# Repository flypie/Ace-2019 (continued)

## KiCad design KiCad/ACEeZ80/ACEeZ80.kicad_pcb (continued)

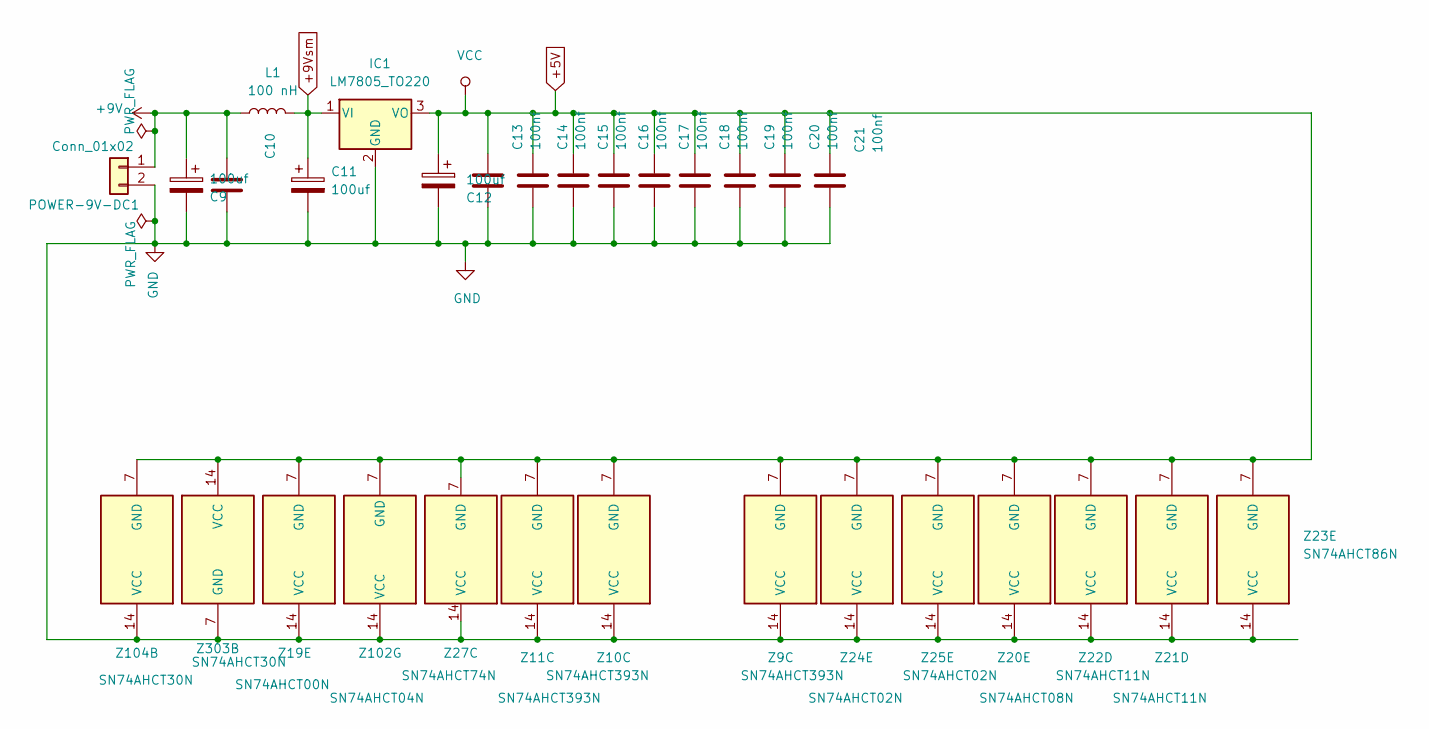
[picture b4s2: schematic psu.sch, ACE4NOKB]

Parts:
C9, C12: 100uf; CP_Radial_D5.0mm_P2.00mm
C10, C13, C14, C15, C16, C17, C18, C19, C20, C21: 100nf; C_Disc_D3.0mm_W1.6mm_P2.50mm; Manufacturer_Part_Number K104K10X7RF53H5
C11: 100uf; CP_Radial_D4.0mm_P1.50mm; Manufacturer_Part_Number K104K10X7RF53H5
IC1: LM7805_TO220; TO-220-3_Vertical
L1: 100 nH; KEMET_SBT_0260T
POWER-9V-DC1: Conn_01x02; CUI_PJ-036C
Z9, Z10, Z11: SN74AHCT393N; DIP-14_W7.62mm
Z19: SN74AHCT00N; DIP-14_W7.62mm
Z20: SN74AHCT08N; DIP-14_W7.62mm
Z21, Z22: SN74AHCT11N; DIP-14_W7.62mm
Z23: SN74AHCT86N; DIP-14_W7.62mm
Z24, Z25: SN74AHCT02N; DIP-14_W7.62mm
Z27: SN74AHCT74N; DIP-14_W7.62mm
Z102: SN74AHCT04N; DIP-14_W7.62mm
Z104: SN74AHCT30N; SOIC-14_3.9x8.7mm_P1.27mm; Manufacturer_Part_Number 74AHCT30D
Z303: SN74AHCT30N; SOIC-14_3.9x8.7mm_P1.27mm

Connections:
+9V: C9.1, C10.1, L1.1, POWER-9V-DC1.1
+9Vsm: C11.1, IC1.1 (VI), L1.2; also elsewhere on the board

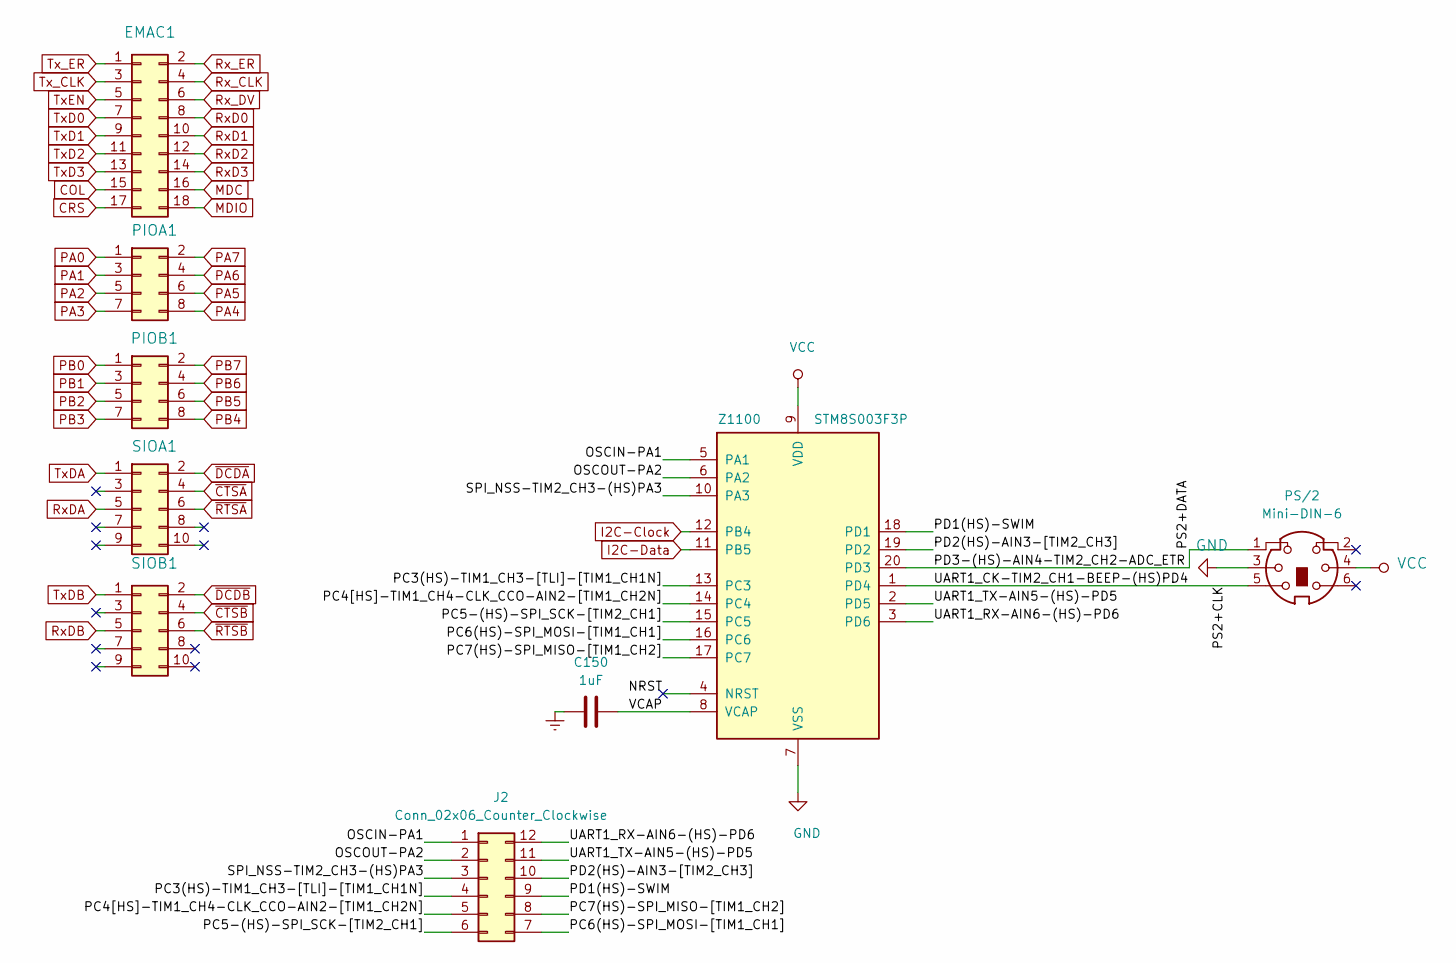
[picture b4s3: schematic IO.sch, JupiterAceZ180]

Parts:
C150: 1uF; C_Disc_D3.8mm_W2.6mm_P2.50mm
EMAC1: 2510-; PinHeader_2x09_P2.54mm_Vertical
J2: Conn_02x06_Counter_Clockwise; PinHeader_2x06_P2.54mm_Vertical
PIOA1: 2510-; PinHeader_2x04_P2.54mm_Vertical
PIOB1: 2510-; PinHeader_2x04_P2.54mm_Vertical
PS/2: Mini-DIN-6; 5749180-1
SIOA1: 2510-; PinHeader_2x05_P2.54mm_Vertical
SIOB1: 2510-; PinHeader_2x05_P2.54mm_Vertical
Z1100: STM8S003F3P; TSSOP-20_4.4x6.5mm_P0.65mm

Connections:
/IO/NRST: Z1100.4 (NRST)
/IO/OSCIN-PA1: J2.1, Z1100.5 (PA1)
/IO/OSCOUT-PA2: J2.2, Z1100.6 (PA2)
/IO/PC3(HS)-TIM1_CH3-[TLI]-[TIM1_CH1N]: J2.4, Z1100.13 (PC3)
/IO/PC4[HS]-TIM1_CH4-CLK_CCO-AIN2-[TIM1_CH2N]: J2.5, Z1100.14 (PC4)
/IO/PC5-(HS)-SPI_SCK-[TIM2_CH1]: J2.6, Z1100.15 (PC5)
/IO/PC6(HS)-SPI_MOSI-[TIM1_CH1]: J2.7, Z1100.16 (PC6)
/IO/PC7(HS)-SPI_MISO-[TIM1_CH2]: J2.8, Z1100.17 (PC7)
/IO/PD1(HS)-SWIM: J2.9, Z1100.18 (PD1)
/IO/PD2(HS)-AIN3-[TIM2_CH3]: J2.10, Z1100.19 (PD2)
/IO/PD3-(HS)-AIN4-TIM2_CH2-ADC_ETR: PS/2.1, Z1100.20 (PD3)
/IO/PS2+CLK: PS/2.5, Z1100.1 (PD4)
/IO/SPI_NSS-TIM2_CH3-(HS)PA3: J2.3, Z1100.10 (PA3)
/IO/UART1_RX-AIN6-(HS)-PD6: J2.12, Z1100.3 (PD6)
/IO/UART1_TX-AIN5-(HS)-PD5: J2.11, Z1100.2 (PD5)
/IO/VCAP: C150.1, Z1100.8 (VCAP)
COL: EMAC1.15; also elsewhere on the board
CRS: EMAC1.17; also elsewhere on the board
Earth: C150.2
I2C-Clock: Z1100.12 (PB4); also elsewhere on the board
I2C-Data: Z1100.11 (PB5); also elsewhere on the board
MDC: EMAC1.16; also elsewhere on the board
MDIO: EMAC1.18; also elsewhere on the board
PA0: PIOA1.1; also elsewhere on the board
PA1: PIOA1.3; also elsewhere on the board
PA2: PIOA1.5; also elsewhere on the board
PA3: PIOA1.7; also elsewhere on the board
PA4: PIOA1.8; also elsewhere on the board
PA5: PIOA1.6; also elsewhere on the board
PA6: PIOA1.4; also elsewhere on the board
PA7: PIOA1.2; also elsewhere on the board
PB0: PIOB1.1; also elsewhere on the board
PB1: PIOB1.3; also elsewhere on the board
PB2: PIOB1.5; also elsewhere on the board
PB3: PIOB1.7; also elsewhere on the board
PB4: PIOB1.8; also elsewhere on the board
PB5: PIOB1.6; also elsewhere on the board
PB6: PIOB1.4; also elsewhere on the board
PB7: PIOB1.2; also elsewhere on the board
RxD0: EMAC1.8; also elsewhere on the board
RxD1: EMAC1.10; also elsewhere on the board
RxD2: EMAC1.12; also elsewhere on the board
RxD3: EMAC1.14; also elsewhere on the board
RxDA: SIOA1.5; also elsewhere on the board
RxDB: SIOB1.5; also elsewhere on the board
Rx_CLK: EMAC1.4; also elsewhere on the board
Rx_DV: EMAC1.6; also elsewhere on the board
Rx_ER: EMAC1.2; also elsewhere on the board
TxD0: EMAC1.7; also elsewhere on the board
TxD1: EMAC1.9; also elsewhere on the board
TxD2: EMAC1.11; also elsewhere on the board
TxD3: EMAC1.13; also elsewhere on the board
TxDA: SIOA1.1; also elsewhere on the board
TxDB: SIOB1.1; also elsewhere on the board
TxEN: EMAC1.5; also elsewhere on the board
Tx_CLK: EMAC1.3; also elsewhere on the board
Tx_ER: EMAC1.1; also elsewhere on the board
~CTSA: SIOA1.4; also elsewhere on the board
~CTSB: SIOB1.4; also elsewhere on the board
~DCDA: SIOA1.2; also elsewhere on the board
~DCDB: SIOB1.2; also elsewhere on the board
~RTSA: SIOA1.6; also elsewhere on the board
~RTSB: SIOB1.6; also elsewhere on the board

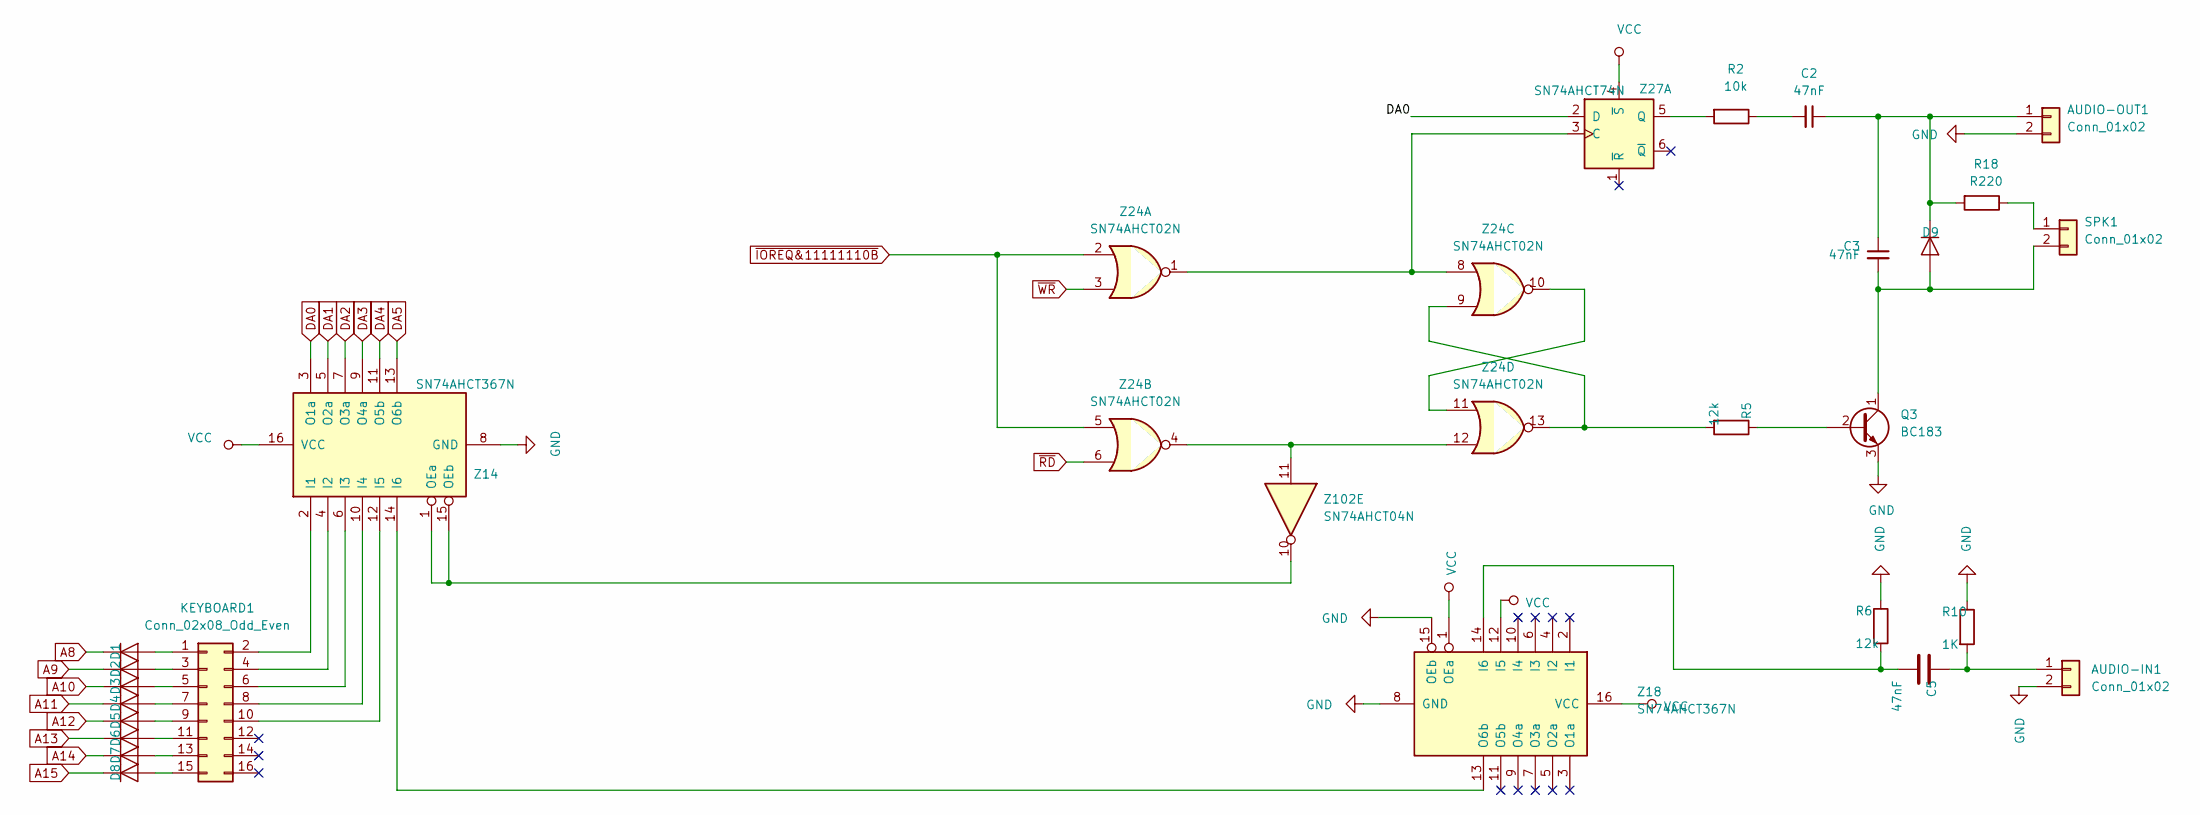
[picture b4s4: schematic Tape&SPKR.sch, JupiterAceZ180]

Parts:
AUDIO-IN1: Conn_01x02; PinHeader_1x02_P2.54mm_Vertical
AUDIO-OUT1: Conn_01x02; PinHeader_1x02_P2.54mm_Vertical
C2, C3, C5: 47nF; C_Disc_D5.0mm_W2.5mm_P5.00mm
D1, D2, D3, D4, D5, D6, D7, D8, D9: 1N4148; D_DO-35_SOD27_P2.54mm_Vertical_AnodeUp
KEYBOARD1: Conn_02x08_Odd_Even; PinHeader_2x08_P2.54mm_Vertical
Q3: BC183; TO-92_Inline
R2: 10k; R_Axial_DIN0204_L3.6mm_D1.6mm_P2.54mm_Vertical
R5, R6: 12k; R_Axial_DIN0204_L3.6mm_D1.6mm_P2.54mm_Vertical
R10: 1K; R_Axial_DIN0204_L3.6mm_D1.6mm_P2.54mm_Vertical
R18: R220; R_Axial_DIN0204_L3.6mm_D1.6mm_P1.90mm_Vertical
SPK1: Conn_01x02; PinHeader_1x02_P2.54mm_Vertical
Z14, Z18: SN74AHCT367N; DIP-16_W7.62mm
Z24: SN74AHCT02N; DIP-14_W7.62mm
Z27: SN74AHCT74N; DIP-14_W7.62mm
Z102: SN74AHCT04N; DIP-14_W7.62mm

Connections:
A8: D1.1 (K); also elsewhere on the board
A9: D2.1 (K); also elsewhere on the board
A10: D3.1 (K); also elsewhere on the board
A11: D4.1 (K); also elsewhere on the board
A12: D5.1 (K); also elsewhere on the board
A13: D6.1 (K); also elsewhere on the board
A14: D7.1 (K); also elsewhere on the board
A15: D8.1 (K); also elsewhere on the board
DA0: Z14.3 (O1a), Z27.2 (D); also elsewhere on the board
DA1: Z14.5 (O2a); also elsewhere on the board
DA2: Z14.7 (O3a); also elsewhere on the board
DA3: Z14.9 (O4a); also elsewhere on the board
DA4: Z14.11 (O5b); also elsewhere on the board
DA5: Z14.13 (O6b); also elsewhere on the board
unnamed: AUDIO-IN1.1, C5.1, R10.2
unnamed: AUDIO-OUT1.1, C2.1, C3.1, D9.1 (K), R18.2
unnamed: C2.2, R2.1
unnamed: C3.2, D9.2 (A), Q3.1 (C), SPK1.2
unnamed: C5.2, R6.2, Z18.14 (I6)
unnamed: D1.2 (A), KEYBOARD1.1
unnamed: D2.2 (A), KEYBOARD1.3
unnamed: D3.2 (A), KEYBOARD1.5
unnamed: D4.2 (A), KEYBOARD1.7
unnamed: D5.2 (A), KEYBOARD1.9
unnamed: D6.2 (A), KEYBOARD1.11
unnamed: D7.2 (A), KEYBOARD1.13
unnamed: D8.2 (A), KEYBOARD1.15
unnamed: KEYBOARD1.2, Z14.2 (I1)
unnamed: KEYBOARD1.4, Z14.4 (I2)
unnamed: KEYBOARD1.6, Z14.6 (I3)
unnamed: KEYBOARD1.8, Z14.10 (I4)
unnamed: KEYBOARD1.10, Z14.12 (I5)
unnamed: Q3.2 (B), R5.1
unnamed: R2.2, Z27.5 (Q)
unnamed: R5.2, Z24.9, Z24.13
unnamed: R18.1, SPK1.1
unnamed: Z14.14 (I6), Z18.13 (O6b)
unnamed: Z24.1, Z24.8, Z27.3 (C)
unnamed: Z24.10, Z24.11
unnamed: Z14.1 (OEa), Z14.15 (OEb), Z102.10
unnamed: Z24.4, Z24.12, Z102.11
~IOREQ&11111110B: Z24.2, Z24.5; also elsewhere on the board
~RD: Z24.6; also elsewhere on the board
~WR: Z24.3; also elsewhere on the board

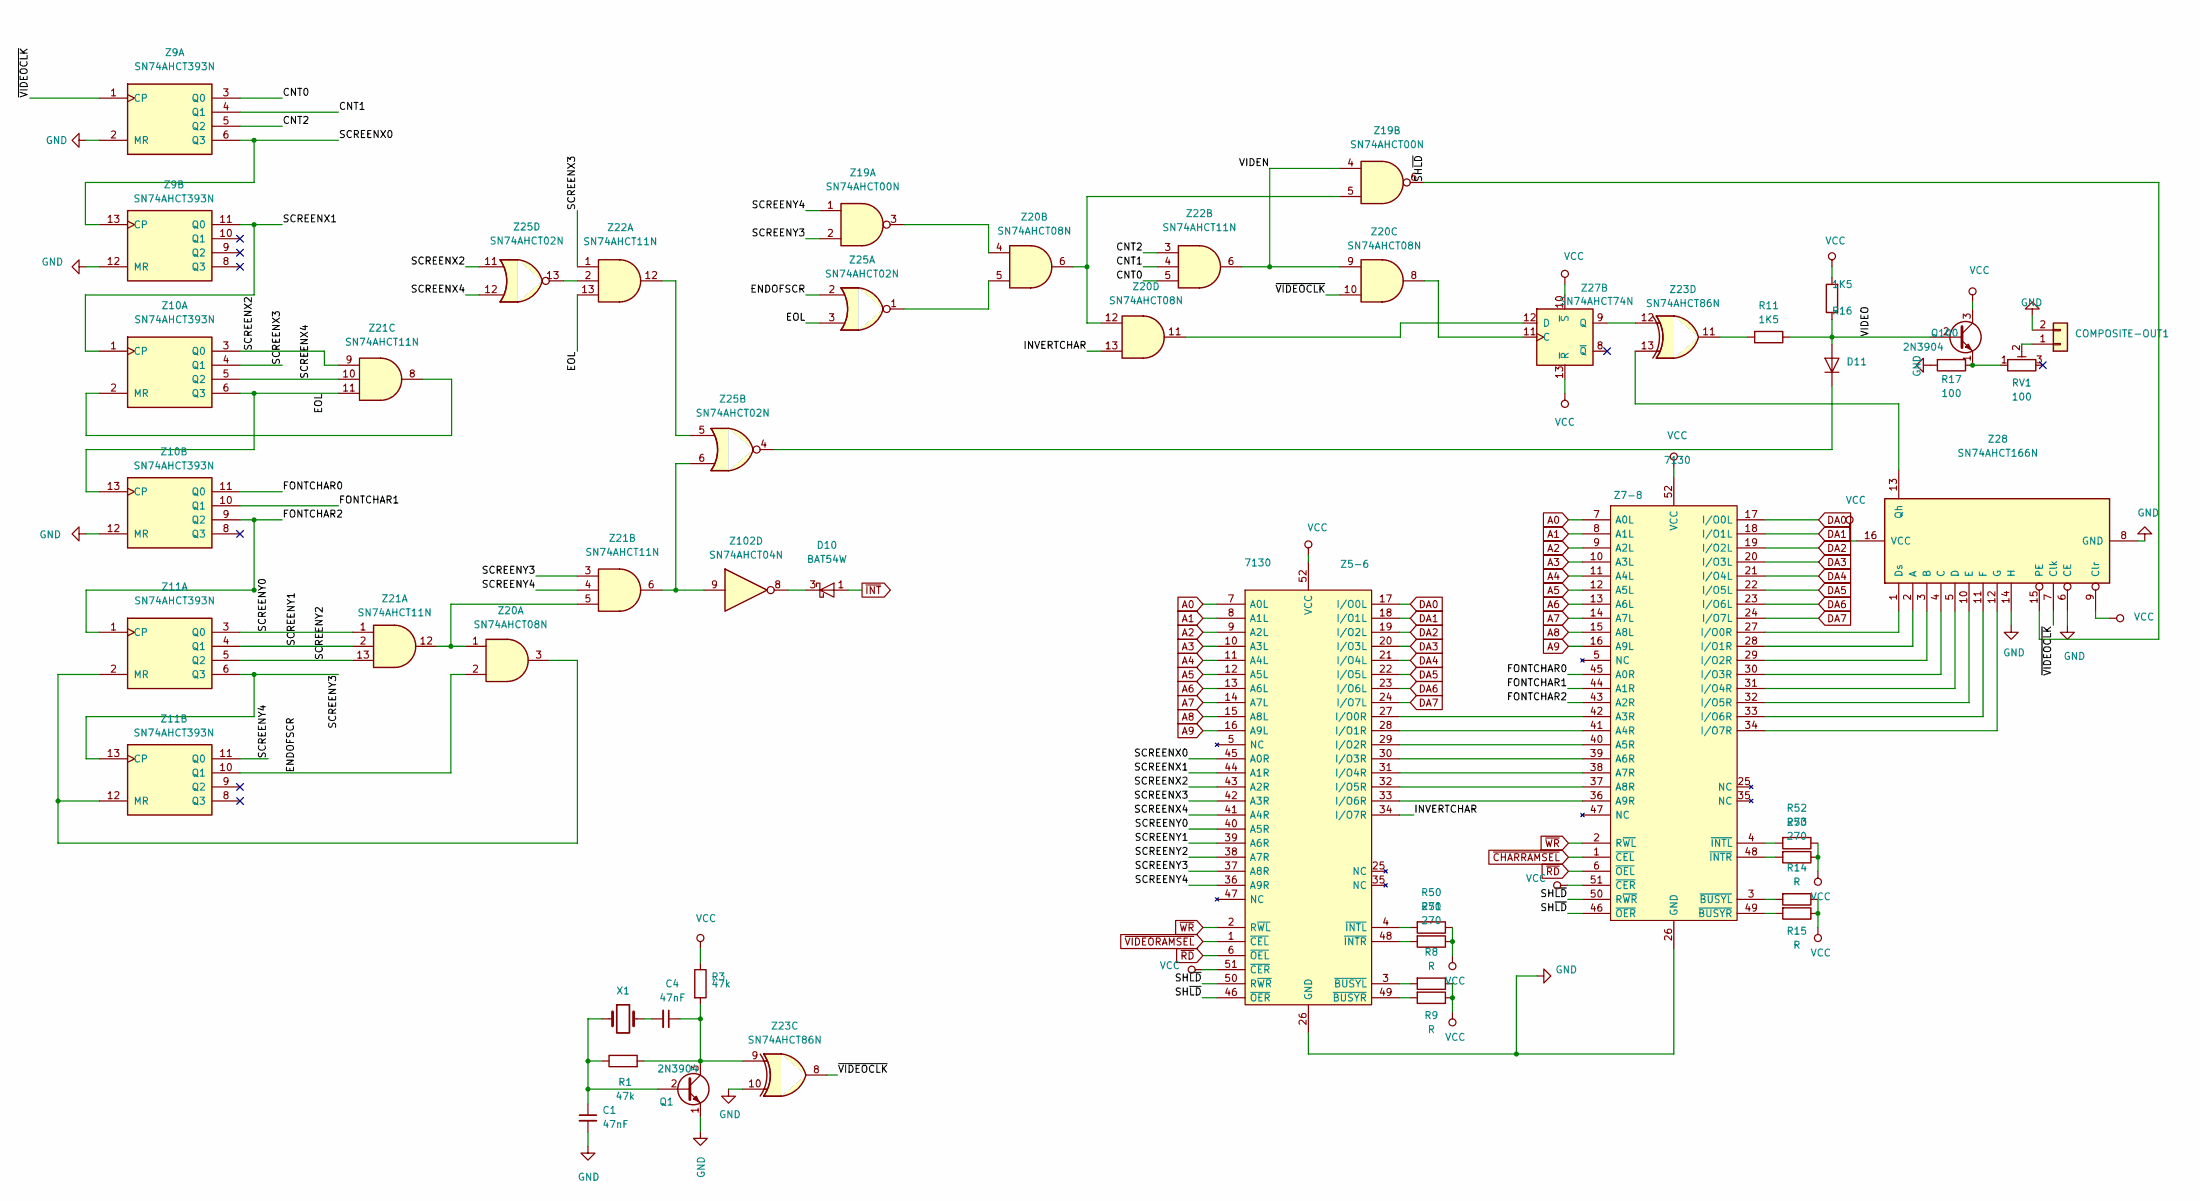
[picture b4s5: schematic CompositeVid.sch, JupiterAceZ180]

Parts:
C1, C4: 47nF; C_Disc_D5.0mm_W2.5mm_P5.00mm
COMPOSITE-OUT1: COMPOSITE-OUT1; PinHeader_1x02_P2.54mm_Vertical
D10: BAT54W; SOT-323_SC-70
D11: 1N4148; D_DO-35_SOD27_P2.54mm_Vertical_AnodeUp
Q1, Q100: 2N3904; TO-92_Inline
R1, R3: 47k; R_Axial_DIN0204_L3.6mm_D1.6mm_P1.90mm_Vertical
R8, R9, R14, R15: R; R_Axial_DIN0204_L3.6mm_D1.6mm_P2.54mm_Vertical
R11, R16: 1K5; R_Axial_DIN0204_L3.6mm_D1.6mm_P2.54mm_Vertical
R17: 100; R_Axial_DIN0204_L3.6mm_D1.6mm_P1.90mm_Vertical
R50, R51, R52, R53: 270; R_Axial_DIN0204_L3.6mm_D1.6mm_P2.54mm_Vertical
RV1: 100; 3362H1103LF
X1: CRYSTALHC49U-V 6.556MHz; Crystal_HC49-U_Vertical
Z5-6, Z7-8: 7130; PLCC-52_THT-Socket; Manufacturer_Part_Number 7132LA100PDG
Z9, Z10, Z11: SN74AHCT393N; DIP-14_W7.62mm
Z19: SN74AHCT00N; DIP-14_W7.62mm
Z20: SN74AHCT08N; DIP-14_W7.62mm
Z21, Z22: SN74AHCT11N; DIP-14_W7.62mm
Z23: SN74AHCT86N; DIP-14_W7.62mm
Z25: SN74AHCT02N; DIP-14_W7.62mm
Z27: SN74AHCT74N; DIP-14_W7.62mm
Z28: SN74AHCT166N; DIP-16_W7.62mm
Z102: SN74AHCT04N; DIP-14_W7.62mm

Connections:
/CompositeVid/CNT0: Z9.3 (Q0), Z22.5
/CompositeVid/CNT1: Z9.4 (Q1), Z22.4
/CompositeVid/CNT2: Z9.5 (Q2), Z22.3
/CompositeVid/ENDOFSCR: Z11.10 (Q1), Z20.2, Z25.2
/CompositeVid/EOL: Z10.6 (Q3), Z10.13 (CP), Z21.11, Z22.13, Z25.3
/CompositeVid/FONTCHAR0: Z7-8.45 (A0R), Z10.11 (Q0)
/CompositeVid/FONTCHAR1: Z7-8.44 (A1R), Z10.10 (Q1)
/CompositeVid/FONTCHAR2: Z7-8.43 (A2R), Z10.9 (Q2), Z11.1 (CP)
/CompositeVid/INVERTCHAR: Z5-6.34 (I/O7R), Z20.13
/CompositeVid/SCREENX0: Z5-6.45 (A0R), Z9.6 (Q3), Z9.13 (CP)
/CompositeVid/SCREENX1: Z5-6.44 (A1R), Z9.11 (Q0), Z10.1 (CP)
/CompositeVid/SCREENX2: Z5-6.43 (A2R), Z10.3 (Q0), Z21.9, Z25.11
/CompositeVid/SCREENX3: Z5-6.42 (A3R), Z10.4 (Q1), Z22.1
/CompositeVid/SCREENX4: Z5-6.41 (A4R), Z10.5 (Q2), Z21.10, Z25.12
/CompositeVid/SCREENY0: Z5-6.40 (A5R), Z11.3 (Q0), Z21.1
/CompositeVid/SCREENY1: Z5-6.39 (A6R), Z11.4 (Q1), Z21.2
/CompositeVid/SCREENY2: Z5-6.38 (A7R), Z11.5 (Q2), Z21.13
/CompositeVid/SCREENY3: Z5-6.37 (A8R), Z11.6 (Q3), Z11.13 (CP), Z19.2, Z21.3
/CompositeVid/SCREENY4: Z5-6.36 (A9R), Z11.11 (Q0), Z19.1, Z21.4
/CompositeVid/SH~LD: Z5-6.46 (~OER), Z5-6.50 (R~WR), Z7-8.46 (~OER), Z7-8.50 (R~WR), Z19.6, Z28.15 (PE)
/CompositeVid/VIDEN: Z19.4, Z20.9, Z22.6
/CompositeVid/VIDEO: D11.2 (A), Q100.2 (B), R11.1, R16.1
/CompositeVid/~VIDEOCLK: Z9.1 (CP), Z20.10, Z23.8, Z28.7 (Clk)
A0: Z5-6.7 (A0L), Z7-8.7 (A0L); also elsewhere on the board
A1: Z5-6.8 (A1L), Z7-8.8 (A1L); also elsewhere on the board
A2: Z5-6.9 (A2L), Z7-8.9 (A2L); also elsewhere on the board
A3: Z5-6.10 (A3L), Z7-8.10 (A3L); also elsewhere on the board
A4: Z5-6.11 (A4L), Z7-8.11 (A4L); also elsewhere on the board
A5: Z5-6.12 (A5L), Z7-8.12 (A5L); also elsewhere on the board
A6: Z5-6.13 (A6L), Z7-8.13 (A6L); also elsewhere on the board
A7: Z5-6.14 (A7L), Z7-8.14 (A7L); also elsewhere on the board
A8: Z5-6.15 (A8L), Z7-8.15 (A8L); also elsewhere on the board
A9: Z5-6.16 (A9L), Z7-8.16 (A9L); also elsewhere on the board
DA0: Z5-6.17 (I/O0L), Z7-8.17 (I/O0L); also elsewhere on the board
DA1: Z5-6.18 (I/O1L), Z7-8.18 (I/O1L); also elsewhere on the board
DA2: Z5-6.19 (I/O2L), Z7-8.19 (I/O2L); also elsewhere on the board
DA3: Z5-6.20 (I/O3L), Z7-8.20 (I/O3L); also elsewhere on the board
DA4: Z5-6.21 (I/O4L), Z7-8.21 (I/O4L); also elsewhere on the board
DA5: Z5-6.22 (I/O5L), Z7-8.22 (I/O5L); also elsewhere on the board
DA6: Z5-6.23 (I/O6L), Z7-8.23 (I/O6L); also elsewhere on the board
DA7: Z5-6.24 (I/O7L), Z7-8.24 (I/O7L); also elsewhere on the board
unnamed: C1.1, Q1.2 (B), R1.1, X1.1
unnamed: C4.1, Q1.3 (C), R1.2, R3.2, Z23.9
unnamed: C4.2, X1.2
unnamed: COMPOSITE-OUT1.1, RV1.2
unnamed: D10.3 (K), Z102.8
unnamed: D11.1 (K), Z25.4
unnamed: Q100.1 (E), R17.1, RV1.1
unnamed: R8.2, Z5-6.3 (~BUSYL)
unnamed: R9.2, Z5-6.49 (~BUSYR)
unnamed: R11.2, Z23.11
unnamed: R14.2, Z7-8.3 (~BUSYL)
unnamed: R15.2, Z7-8.49 (~BUSYR)
unnamed: R50.2, Z5-6.4 (~INTL)
unnamed: R51.2, Z5-6.48 (~INTR)
unnamed: R52.2, Z7-8.4 (~INTL)
unnamed: R53.2, Z7-8.48 (~INTR)
unnamed: Z5-6.27 (I/O0R), Z7-8.42 (A3R)
unnamed: Z5-6.28 (I/O1R), Z7-8.41 (A4R)
unnamed: Z5-6.29 (I/O2R), Z7-8.40 (A5R)
unnamed: Z5-6.30 (I/O3R), Z7-8.39 (A6R)
unnamed: Z5-6.31 (I/O4R), Z7-8.38 (A7R)
unnamed: Z5-6.32 (I/O5R), Z7-8.37 (A8R)
unnamed: Z5-6.33 (I/O6R), Z7-8.36 (A9R)
unnamed: Z10.2 (MR), Z21.8
unnamed: Z11.2 (MR), Z11.12 (MR), Z20.3
unnamed: Z19.3, Z20.4
unnamed: Z19.5, Z20.6, Z20.12
unnamed: Z20.1, Z21.5, Z21.12
unnamed: Z20.5, Z25.1
unnamed: Z20.8, Z27.11 (C)
unnamed: Z20.11, Z27.12 (D)
unnamed: Z22.2, Z25.13
unnamed: Z22.12, Z25.5
unnamed: Z23.12, Z27.9 (Q)
unnamed: Z23.13, Z28.13 (Qh)
unnamed: Z7-8.27 (I/O0R), Z28.1 (Ds)
unnamed: Z7-8.28 (I/O1R), Z28.2 (A)
unnamed: Z7-8.29 (I/O2R), Z28.3 (B)
unnamed: Z7-8.30 (I/O3R), Z28.4 (C)
unnamed: Z7-8.31 (I/O4R), Z28.5 (D)
unnamed: Z7-8.32 (I/O5R), Z28.10 (E)
unnamed: Z7-8.33 (I/O6R), Z28.11 (F)
unnamed: Z7-8.34 (I/O7R), Z28.12 (G)
unnamed: Z21.6, Z25.6, Z102.9
~CHARRAMSEL: Z7-8.1 (~CEL); also elsewhere on the board
~INT: D10.1 (A); also elsewhere on the board
~RD: Z5-6.6 (~OEL), Z7-8.6 (~OEL); also elsewhere on the board
~VIDEORAMSEL: Z5-6.1 (~CEL); also elsewhere on the board
~WR: Z5-6.2 (R~WL), Z7-8.2 (R~WL); also elsewhere on the board

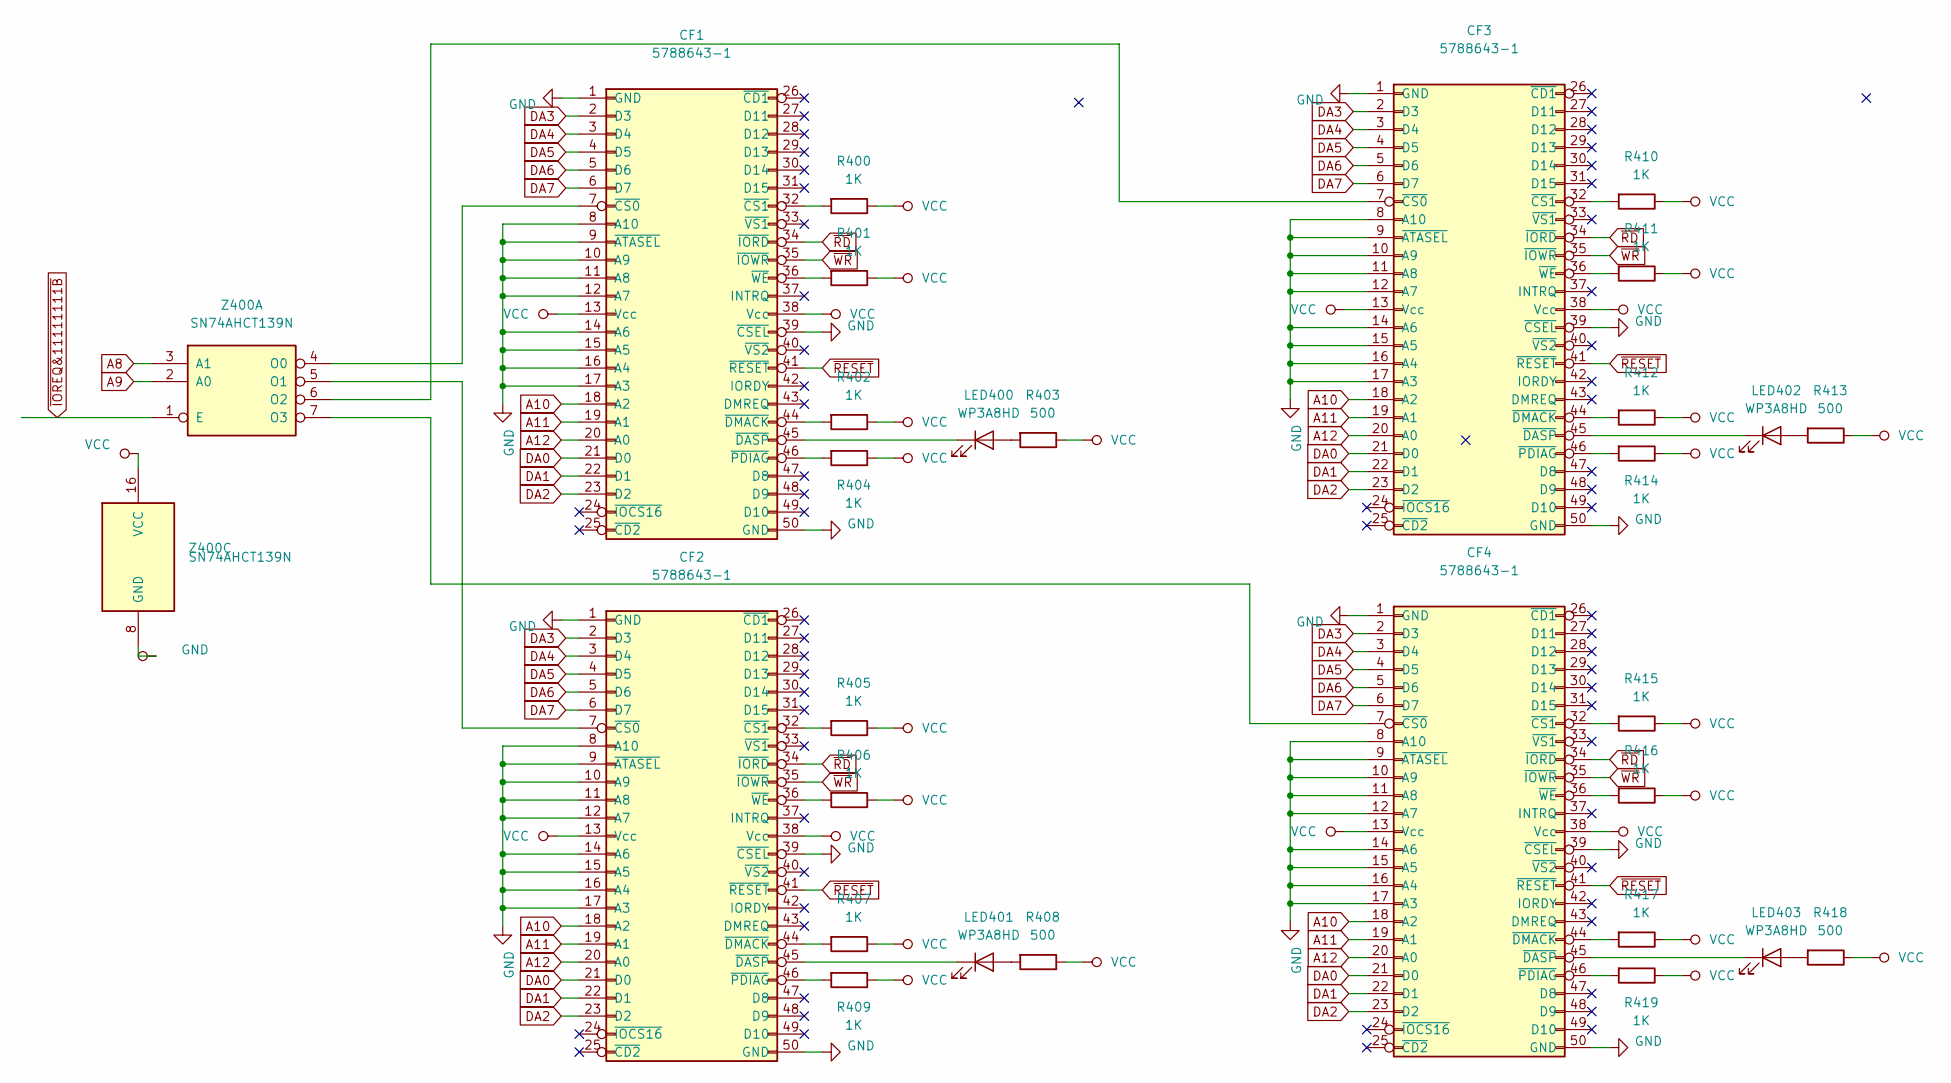
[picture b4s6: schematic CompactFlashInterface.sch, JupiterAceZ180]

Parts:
CF1, CF2, CF3, CF4: 5788643-1; 57886431; Manufacturer_Part_Number 5788643-1; Mouser Part Number 571-5788643-1
LED400, LED401, LED402, LED403: WP3A8HD; LED_D3.0mm
R400, R401, R402, R404, R405, R406, R407, R409, R410, R411, R412, R414, R415, R416, R417, R419: 1K; R_Axial_DIN0204_L3.6mm_D1.6mm_P1.90mm_Vertical
R403, R408, R413, R418: 500; R_Axial_DIN0204_L3.6mm_D1.6mm_P1.90mm_Vertical
Z400: SN74AHCT139N; DIP-16_W7.62mm

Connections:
A8: Z400.3 (A1); also elsewhere on the board
A9: Z400.2 (A0); also elsewhere on the board
A10: CF1.18 (A2), CF2.18 (A2), CF3.18 (A2), CF4.18 (A2); also elsewhere on the board
A11: CF1.19 (A1), CF2.19 (A1), CF3.19 (A1), CF4.19 (A1); also elsewhere on the board
A12: CF1.20 (A0), CF2.20 (A0), CF3.20 (A0), CF4.20 (A0); also elsewhere on the board
DA0: CF1.21 (D0), CF2.21 (D0), CF3.21 (D0), CF4.21 (D0); also elsewhere on the board
DA1: CF1.22 (D1), CF2.22 (D1), CF3.22 (D1), CF4.22 (D1); also elsewhere on the board
DA2: CF1.23 (D2), CF2.23 (D2), CF3.23 (D2), CF4.23 (D2); also elsewhere on the board
DA3: CF1.2 (D3), CF2.2 (D3), CF3.2 (D3), CF4.2 (D3); also elsewhere on the board
DA4: CF1.3 (D4), CF2.3 (D4), CF3.3 (D4), CF4.3 (D4); also elsewhere on the board
DA5: CF1.4 (D5), CF2.4 (D5), CF3.4 (D5), CF4.4 (D5); also elsewhere on the board
DA6: CF1.5 (D6), CF2.5 (D6), CF3.5 (D6), CF4.5 (D6); also elsewhere on the board
DA7: CF1.6 (D7), CF2.6 (D7), CF3.6 (D7), CF4.6 (D7); also elsewhere on the board
unnamed: CF1.7 (~CS0), Z400.4 (O0)
unnamed: CF1.32 (~CS1), R400.2
unnamed: CF1.36 (~WE), R401.2
unnamed: CF1.44 (~DMACK), R402.2
unnamed: CF1.45 (~DASP), LED400.1 (K)
unnamed: CF1.46 (~PDIAG), R404.2
unnamed: CF2.7 (~CS0), Z400.5 (O1)
unnamed: CF2.32 (~CS1), R405.2
unnamed: CF2.36 (~WE), R406.2
unnamed: CF2.44 (~DMACK), R407.2
unnamed: CF2.45 (~DASP), LED401.1 (K)
unnamed: CF2.46 (~PDIAG), R409.2
unnamed: CF3.7 (~CS0), Z400.6 (O2)
unnamed: CF3.32 (~CS1), R410.2
unnamed: CF3.36 (~WE), R411.2
unnamed: CF3.44 (~DMACK), R412.2
unnamed: CF3.45 (~DASP), LED402.1 (K)
unnamed: CF3.46 (~PDIAG), R414.2
unnamed: CF4.7 (~CS0), Z400.7 (O3)
unnamed: CF4.32 (~CS1), R415.2
unnamed: CF4.36 (~WE), R416.2
unnamed: CF4.44 (~DMACK), R417.2
unnamed: CF4.45 (~DASP), LED403.1 (K)
unnamed: CF4.46 (~PDIAG), R419.2
unnamed: LED400.2 (A), R403.2
unnamed: LED401.2 (A), R408.2
unnamed: LED402.2 (A), R413.2
unnamed: LED403.2 (A), R418.2
~IOREQ&11111111B: Z400.1 (E); also elsewhere on the board
~RD: CF1.34 (~IORD), CF2.34 (~IORD), CF3.34 (~IORD), CF4.34 (~IORD); also elsewhere on the board
~RESET: CF1.41 (~RESET), CF2.41 (~RESET), CF3.41 (~RESET), CF4.41 (~RESET); also elsewhere on the board
~WR: CF1.35 (~IOWR), CF2.35 (~IOWR), CF3.35 (~IOWR), CF4.35 (~IOWR); also elsewhere on the board

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
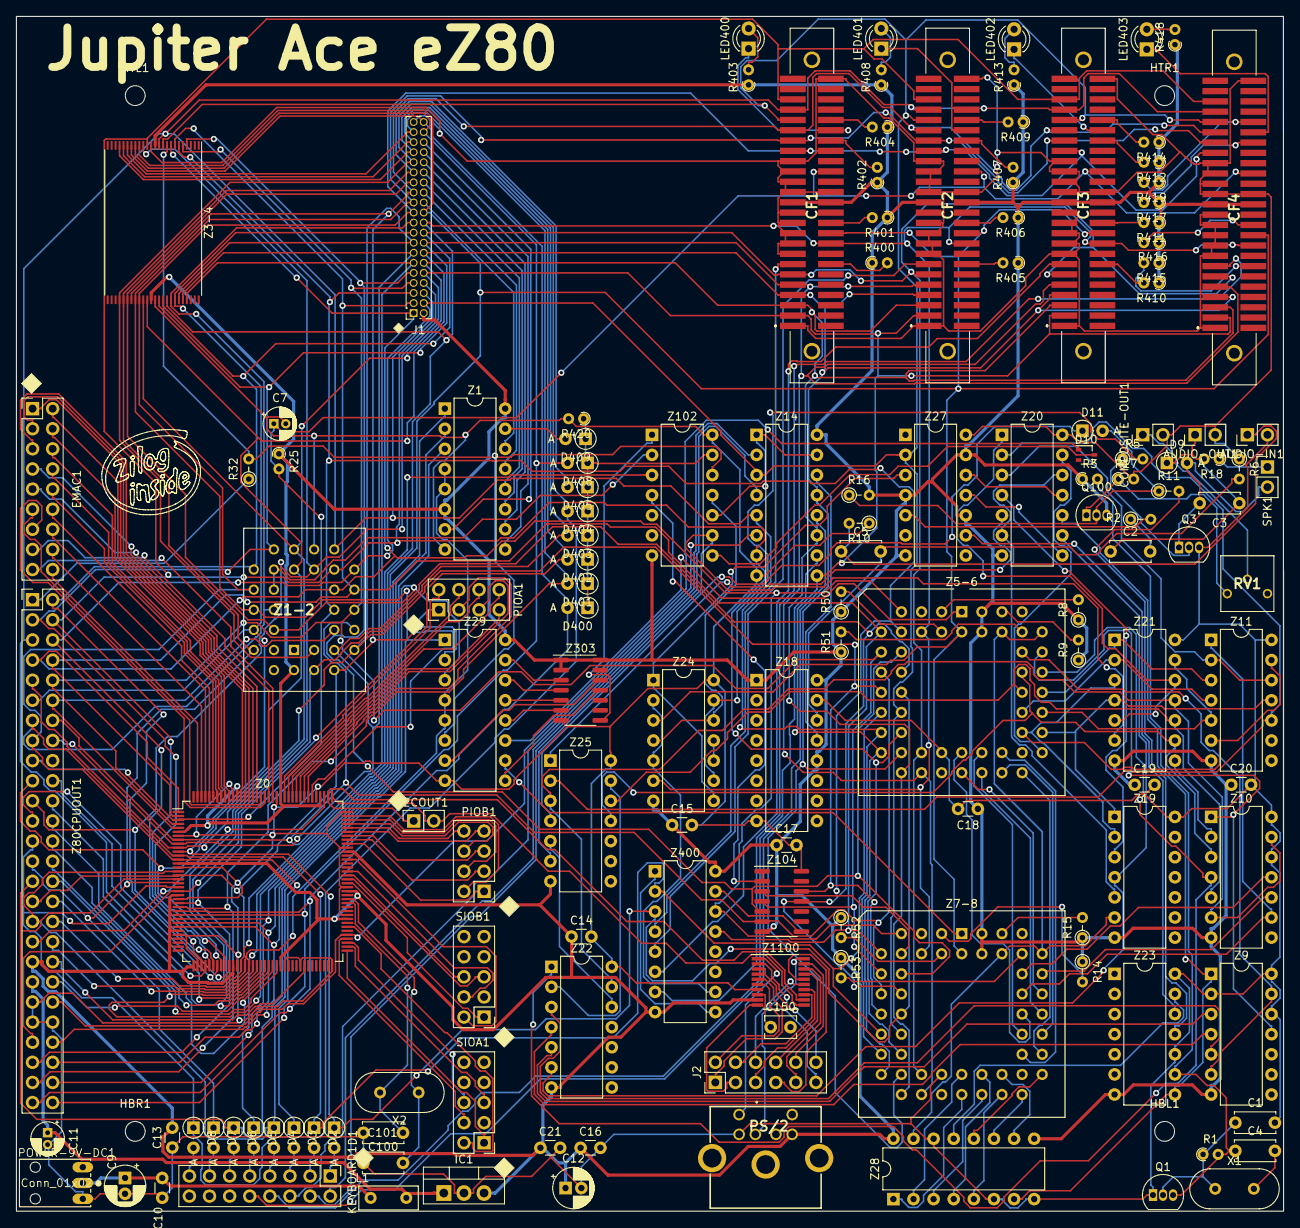
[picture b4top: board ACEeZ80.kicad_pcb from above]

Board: 2 copper layers, 160.0 x 150.9 mm, 146 parts (0 on the bottom side), 259 nets.

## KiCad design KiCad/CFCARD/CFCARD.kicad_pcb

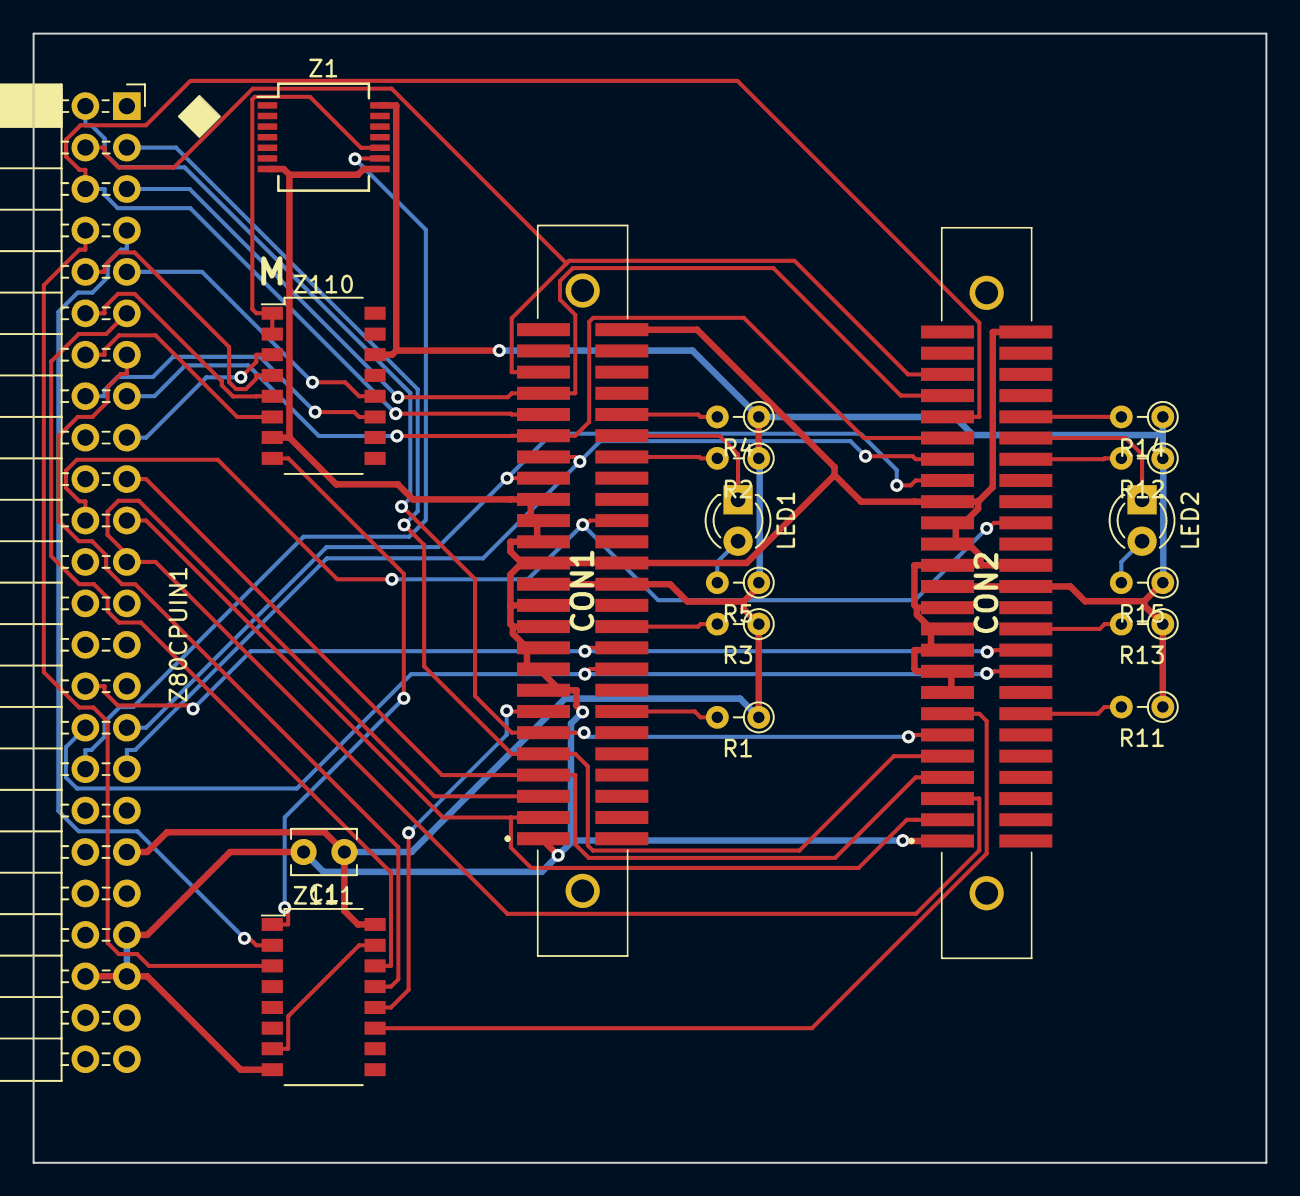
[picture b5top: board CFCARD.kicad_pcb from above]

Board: 2 copper layers, 75.6 x 69.2 mm, 19 parts (0 on the bottom side), 44 nets.

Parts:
C1: 0.1 uF; C_Disc_D3.8mm_W2.6mm_P2.50mm
CON1, CON2: 5788643-1; 57886431
LED1, LED2: LED; LED_D3.0mm
R1, R2, R3, R4, R11, R12, R13, R14: 1K; R_Axial_DIN0204_L3.6mm_D1.6mm_P2.54mm_Vertical
R5, R15: 560; R_Axial_DIN0204_L3.6mm_D1.6mm_P2.54mm_Vertical
Z1: SN74AHCT02PWR; SSOP-14_5.3x6.2mm_P0.65mm
Z80CPUIN1: Conn_02x24_Odd_Even; PinSocket_2x24_P2.54mm_Horizontal
Z110: 74AHCT30PW,118; SOP-16_4.4x10.4mm_P1.27mm
Z111: SN74AHCT139D; SOP-16_4.4x10.4mm_P1.27mm

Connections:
/A0: Z80CPUIN1.7, Z111.2 (A0)
/A1: Z80CPUIN1.8, Z111.3 (A1)
/A2: Z80CPUIN1.17, Z110.3
/A3: Z80CPUIN1.10, Z110.4
/A4: Z80CPUIN1.12, Z110.5
/A5: Z80CPUIN1.14, Z110.6
/A6: Z80CPUIN1.16, Z110.11
/A7: Z80CPUIN1.9, Z110.12
/A8: Z80CPUIN1.11, Z111.14 (A0)
/A9: Z80CPUIN1.13, Z111.13 (A1)
/A10: CON1.20 (A0), CON2.20 (A0), Z80CPUIN1.15
/A11: CON1.19 (A1), CON2.19 (A1), Z80CPUIN1.33
/A12: CON1.18 (A2), CON2.18 (A2), Z80CPUIN1.31
/DA0: CON1.21 (D0), CON2.21 (D0), Z80CPUIN1.6
/DA1: CON1.22 (D1), CON2.22 (D1), Z80CPUIN1.5
/DA2: CON1.23 (D2), CON2.23 (D2), Z80CPUIN1.4
/DA3: CON1.2 (D3), CON2.2 (D3), Z80CPUIN1.21
/DA4: CON1.3 (D4), CON2.3 (D4), Z80CPUIN1.23
/DA5: CON1.4 (D5), CON2.4 (D5), Z80CPUIN1.19
/DA6: CON1.5 (D6), CON2.5 (D6), Z80CPUIN1.3
/DA7: CON1.6 (D7), CON2.6 (D7), Z80CPUIN1.2
/PS2-Socket: Z111.7 (O3), Z111.15 (E)
/~IOREQ: Z1.9, Z80CPUIN1.34
/~RD: CON1.34 (~IORD), CON2.34 (~IORD), Z80CPUIN1.32
/~RESET: CON1.41 (~RESET), CON2.41 (~RESET), Z80CPUIN1.22
/~WR: CON1.35 (~IOWR), CON2.35 (~IOWR), Z80CPUIN1.30
GND: C1.2, CON1.1 (GND), CON1.8 (A10), CON1.9 (~ATASEL), CON1.10 (A9), CON1.11 (A8), CON1.12 (A7), CON1.14 (A6), CON1.15 (A5), CON1.16 (A4), CON1.17 (A3), CON1.39 (~CSEL), CON1.50 (GND), CON2.1 (GND), CON2.8 (A10), CON2.9 (~ATASEL), CON2.10 (A9), CON2.11 (A8), CON2.12 (A7), CON2.14 (A6), CON2.15 (A5), CON2.16 (A4), CON2.17 (A3), CON2.39 (~CSEL), CON2.50 (GND), Z1.7 (GND), Z1.8, Z80CPUIN1.41, Z80CPUIN1.43, Z80CPUIN1.44, Z110.7 (GND), Z111.8 (GND)
unnamed: CON1.7 (~CS0), Z111.12 (O0)
unnamed: CON1.32 (~CS1), R1.2
unnamed: CON1.36 (~WE), R3.2
unnamed: CON1.44 (~DMACK), R2.2
unnamed: CON1.45 (~DASP), LED1.1 (K)
unnamed: CON1.46 (~PDIAG), R4.2
unnamed: CON2.7 (~CS0), Z111.11 (O1)
unnamed: CON2.32 (~CS1), R11.2
unnamed: CON2.36 (~WE), R13.2
unnamed: CON2.44 (~DMACK), R12.2
unnamed: CON2.45 (~DASP), LED2.1 (K)
unnamed: CON2.46 (~PDIAG), R14.2
unnamed: LED1.2 (A), R5.2
unnamed: LED2.2 (A), R15.2
unnamed: Z1.10, Z110.1, Z110.2
unnamed: Z110.8, Z111.1 (E)
VCC: C1.1, CON1.13 (Vcc), CON1.38 (Vcc), CON2.13 (Vcc), CON2.38 (Vcc), R1.1, R2.1, R3.1, R4.1, R5.1, R11.1, R12.1, R13.1, R14.1, R15.1, Z1.14 (VCC), Z80CPUIN1.37, Z110.14 (VCC), Z111.16 (VCC)
